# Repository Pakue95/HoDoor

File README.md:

HoDoor is an access control board that uses RFID (13.56MHz) to authenticate users e.g. to enter restricted areas. The firmware repository can be found [here]() (to be released).

## ToDo
* generate Gerber files
* generate new 3d STEP files
* update case-files to v2.1

The work is release as is without any warranties or guarantees. Use on your own risk.

## Hardware

## License

Designed by Patrick Kübler (except for Adafruit PN532 Shield part). Creative Commons Attribution/Share-Alike.

### Adafruit PN532 RFID/NFC Shield for Arduino

The NFC part of the board is based upon the Adafruit PN532 RFID/NFC Shield for Arduino. The design files can be found in the according [repository](https://github.com/adafruit/Adafruit-PN532-RFID-NFC-Shield) and the board can be purchased from [Adafruit](https://www.adafruit.com/product/789).

Following changes were made from the Adafruit design:
* Moved pinheader around (no Arduino Shield compatebility anymore)
* Moved some components and routing
* removed LED power indicator
* no prototyping area
* removed 3.3V regulator (handled by the HoDoor board)

**README from Adafruit PN532 Shield**

>We've taken our popular Adafruit PN532 breakout board and turned it into a shield - the perfect tool for any 13.56MHz RFID or NFC application. The Adafruit NFC shield uses the PN532 chip-set (the most popular NFC chip on the market) and is what is embedded in pretty much every phone or device that does NFC. It can pretty much do it all, such as read and write to tags and cards, communicate with phones (say for payment processing), and 'act' like a NFC tag. If you want to do any sort of embedded NFC work, this is the chip you'll want to use!

>These are the Eagle CAD files for the Adafruit PN532 RFID/NFC Shield for Arduino:

>* http://www.adafruit.com/products/789

>License

>Adafruit invests time and resources providing this open source design, please support Adafruit and open-source hardware by purchasing products from Adafruit!

>All text above must be included in any redistribution

>Designed by Limor Fried/Ladyada and Kevin Townsend for Adafruit Industries. Creative Commons Attribution/Share-Alike, all text above must be included in any redistribution. See license.txt for additional information.

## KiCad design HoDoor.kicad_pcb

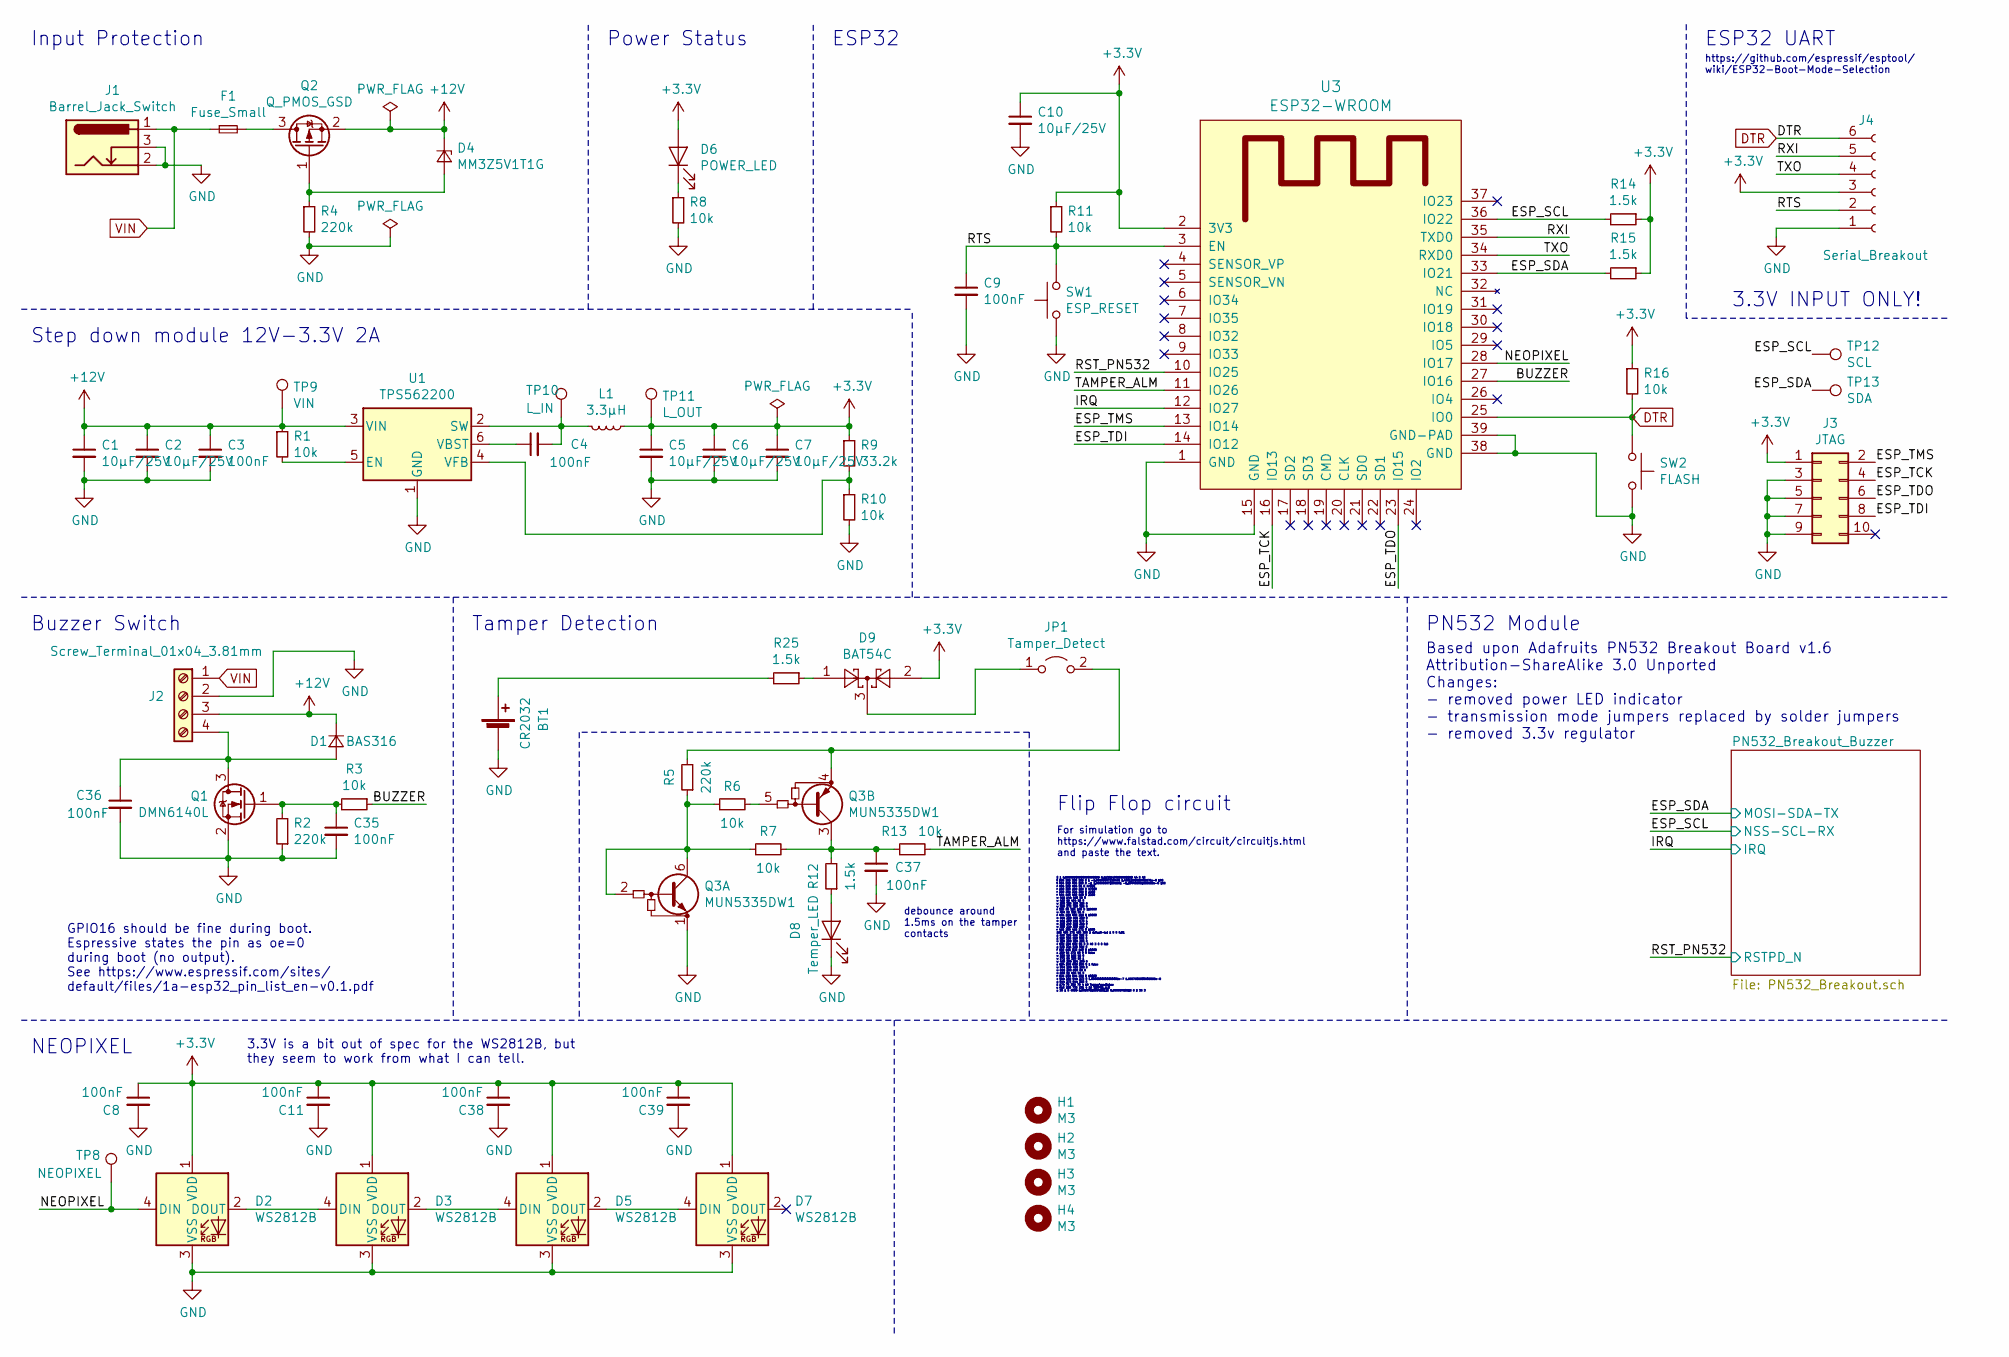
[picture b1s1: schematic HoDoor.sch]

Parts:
BT1: CR2032; BatteryHolder_Keystone_1060_1x2032; Part CR2032-BS-6-1; LCSC C70377
C1, C2, C5, C6, C7, C10: 10µF/25V; C_1206_3216Metric; Part CL31B106KAHVPNE; LCSC C9807
C3, C4, C8, C9, C11, C35, C36, C37, C38, C39: 100nF; C_0603_1608Metric; Part CL10B104KA8NNNC; LCSC C1590
D1: BAS316; D_SOD-323; Part BAS316,115; LCSC C109218
D2, D3, D5, D7: WS2812B; LED_WS2812B_PLCC4_5.0x5.0mm_P3.2mm
D4: MM3Z5V1T1G; D_SOD-323; Part MM3Z5V1T1G; LCSC C75074
D6: POWER_LED; LED_0805_2012Metric_Pad1.15x1.40mm_HandSolder; Part FC-2012HRK-620D; LCSC C84256
D8: Temper_LED; LED_0805_2012Metric_Pad1.15x1.40mm_HandSolder; Part TJ-S2012SW8TGLC0A-A5 TJ-S2012SW8TGLC0A-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; LCSC C192670
D9: BAT54C; SOT-23; LCSC C37704
F1: Fuse_Small; Fuse_1206_3216Metric_Pad1.42x1.75mm_HandSolder
H1, H2, H3, H4: M3; MountingHole_3.2mm_M3_DIN965_Pad
J1: Barrel_Jack_Switch; BarrelJack_Horizontal
J2: Screw_Terminal_01x04_3.81mm; WJ15EDGRC-3.81-4P; Part WJ15EDGRC-3.81-4P + WJ15EDGKB-3.81-4P; LCSC C7245 + C8408
J3: JTAG; Tag-Connect_TC2050-IDC-FP_2x05_P1.27mm_Vertical
J4: Serial_Breakout; PinHeader_1x06_P2.54mm_Horizontal; Part A2541WR-6P; LCSC C225492
JP1: Tamper_Detect; SW_SPST_B3S-1000
L1: 3.3µH; NPIS43LS; Part NPIS43LS3R3MTRF
Q1: DMN6140L; SOT-23; Part DMN6140LQ-7; LCSC C155271
Q2: Q_PMOS_GSD; SOT-23; Part AO3401A; LCSC C15127
Q3: MUN5335DW1; SOT-363_SC-70-6; Part MUN5335DW1T1G; LCSC C99680
R1, R3, R6, R7, R10, R11, R13, R16: 10k; R_0603_1608Metric; Part RC0603FR-0710KL; LCSC C98220
R2, R4, R5: 220k; R_0603_1608Metric; Part RC0603FR-07220KL; LCSC C123420
R8: 10k; R_0603_1608Metric; Part RC0603JR-07330RL; LCSC C105879
R9: 33.2k; R_0603_1608Metric; Part AC0603FR-0733K2L; LCSC C227824
R12, R14, R15, R25: 1.5k; R_0603_1608Metric; Part RC0603FR-071K5L; LCSC C114668
SW1: ESP_RESET; SW_SPST_B3S-1000; Part TSA063G43-250; LCSC C294564
SW2: FLASH; SW_SPST_B3S-1000; Part TSA063G43-250; LCSC C294564
TP8: NEOPIXEL; TestPoint_Pad_D1.0mm
TP9: VIN; TestPoint_Pad_D1.0mm
TP10: L_IN; TestPoint_Pad_D1.0mm
TP11: L_OUT; TestPoint_Pad_D1.0mm
TP12: SCL; TestPoint_Pad_D1.0mm
TP13: SDA; TestPoint_Pad_D1.0mm
U1: TPS562200; SOT-23-6; Part TPS562200DDCR; LCSC C49757
U3: ESP32-WROOM

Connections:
+12V: C1.1, C2.1, C3.1, D1.1 (K), D4.1 (K), J2.3, Q2.2 (S), R1.1, TP9.1, U1.3 (VIN)
/BUZZER: R3.1, U3.27 (IO16)
/ESP_SCL: R14.2, TP12.1, U3.36 (IO22); also elsewhere on the board
/ESP_SDA: R15.2, TP13.1, U3.33 (IO21); also elsewhere on the board
/ESP_TCK: J3.4, U3.16 (IO13)
/ESP_TDI: J3.8, U3.14 (IO12)
/ESP_TDO: J3.6, U3.23 (IO15)
/ESP_TMS: J3.2, U3.13 (IO14)
/IRQ: U3.12 (IO27); also elsewhere on the board
/NEOPIXEL: D2.4 (DIN), TP8.1, U3.28 (IO17)
/RST_PN532: U3.10 (IO25); also elsewhere on the board
/RTS: C9.1, J4.2, R11.2, SW1.2, U3.3 (EN)
/RXI: J4.5, U3.35 (TXD0)
/TAMPER_ALM: R13.2, U3.11 (IO26)
/TXO: J4.4, U3.34 (RXD0)
DTR: J4.6, R16.2, SW2.1, U3.25 (IO0)
GND: BT1.2 (-), C1.2, C2.2, C3.2, C5.2, C6.2, C7.2, C8.2, C9.2, C10.2, C11.2, C35.2, C36.2, C37.2, C38.2, C39.2, D2.3 (VSS), D3.3 (VSS), D5.3 (VSS), D7.3 (VSS), D8.1 (K), J1.2, J1.3, J2.2, J3.3, J3.5, J3.7, J3.9, J4.1, Q1.2 (S), Q3.1 (E1), R2.1, R4.2, R8.2, R10.2, SW1.1, SW2.2, U1.1 (GND), U3.1 (GND), U3.15 (GND), U3.38 (GND), U3.39 (GND-PAD); also elsewhere on the board
unnamed: BT1.1 (+), R25.2
unnamed: C4.1, U1.6 (VBST)
unnamed: C4.2, L1.2, TP10.1, U1.2 (SW)
unnamed: C35.1, Q1.1 (G), R2.2, R3.2
unnamed: C36.1, D1.2 (A), J2.4, Q1.3 (D)
unnamed: C37.1, Q3.3 (C1), R7.2, R12.2, R13.1
unnamed: D2.2 (DOUT), D3.4 (DIN)
unnamed: D3.2 (DOUT), D5.4 (DIN)
unnamed: D4.2 (A), Q2.1 (G), R4.1
unnamed: D5.2 (DOUT), D7.4 (DIN)
unnamed: D6.1 (K), R8.1
unnamed: D8.2 (A), R12.1
unnamed: D9.1, R25.1
unnamed: D9.3, JP1.1 (A)
unnamed: F1.2, Q2.3 (D)
unnamed: JP1.2 (B), Q3.4 (E1), R5.2
unnamed: Q3.2 (B1), Q3.6 (C1), R5.1, R6.1, R7.1
unnamed: Q3.5 (B1), R6.2
unnamed: R1.2, U1.5 (EN)
unnamed: R9.2, R10.1, U1.4 (VFB)
VIN: F1.1, J1.1, J2.1

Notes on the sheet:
Step down module 12V-3.3V 2A
GPIO16 should be fine during boot. Espressive states the pin as oe=0 during boot (no output). See https://www.espressif.com/sites/ default/files/1a-esp32_pin_list_en-v0.1.pdf
3.3V INPUT ONLY!
Input Protection
Power Status
Buzzer Switch
Tamper Detection
PN532 Module
ESP32 UART
NEOPIXEL
https://github.com/espressif/esptool/ wiki/ESP32-Boot-Mode-Selection
$ 1 0.00009999999999999999 0.11331484530668263 44 5 43 t 288 256 320 256 0 1 -2.99999997233476 1.4381236668005676e-8 100 t 464 160 496 160 0 -1 2.999999971598301 -1.154406081838033e-8 100 r 464 160 464 96 0 47000 r 288 320 288 256 0 47000 r 288 256 224 256 0 2200 r 464 160 400 160 0 2200 w 496 144 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
For simulation go to https://www.falstad.com/circuit/circuitjs.html and paste the text.
ESP32
Flip Flop circuit
debounce around 1.5ms on the tamper contacts
3.3V is a bit out of spec for the WS2812B, but they seem to work from what I can tell.
Based upon Adafruits PN532 Breakout Board v1.6 Attribution-ShareAlike 3.0 Unported Changes: - removed power LED indicator - transmission mode jumpers replaced by solder jumpers - removed 3.3v regulator

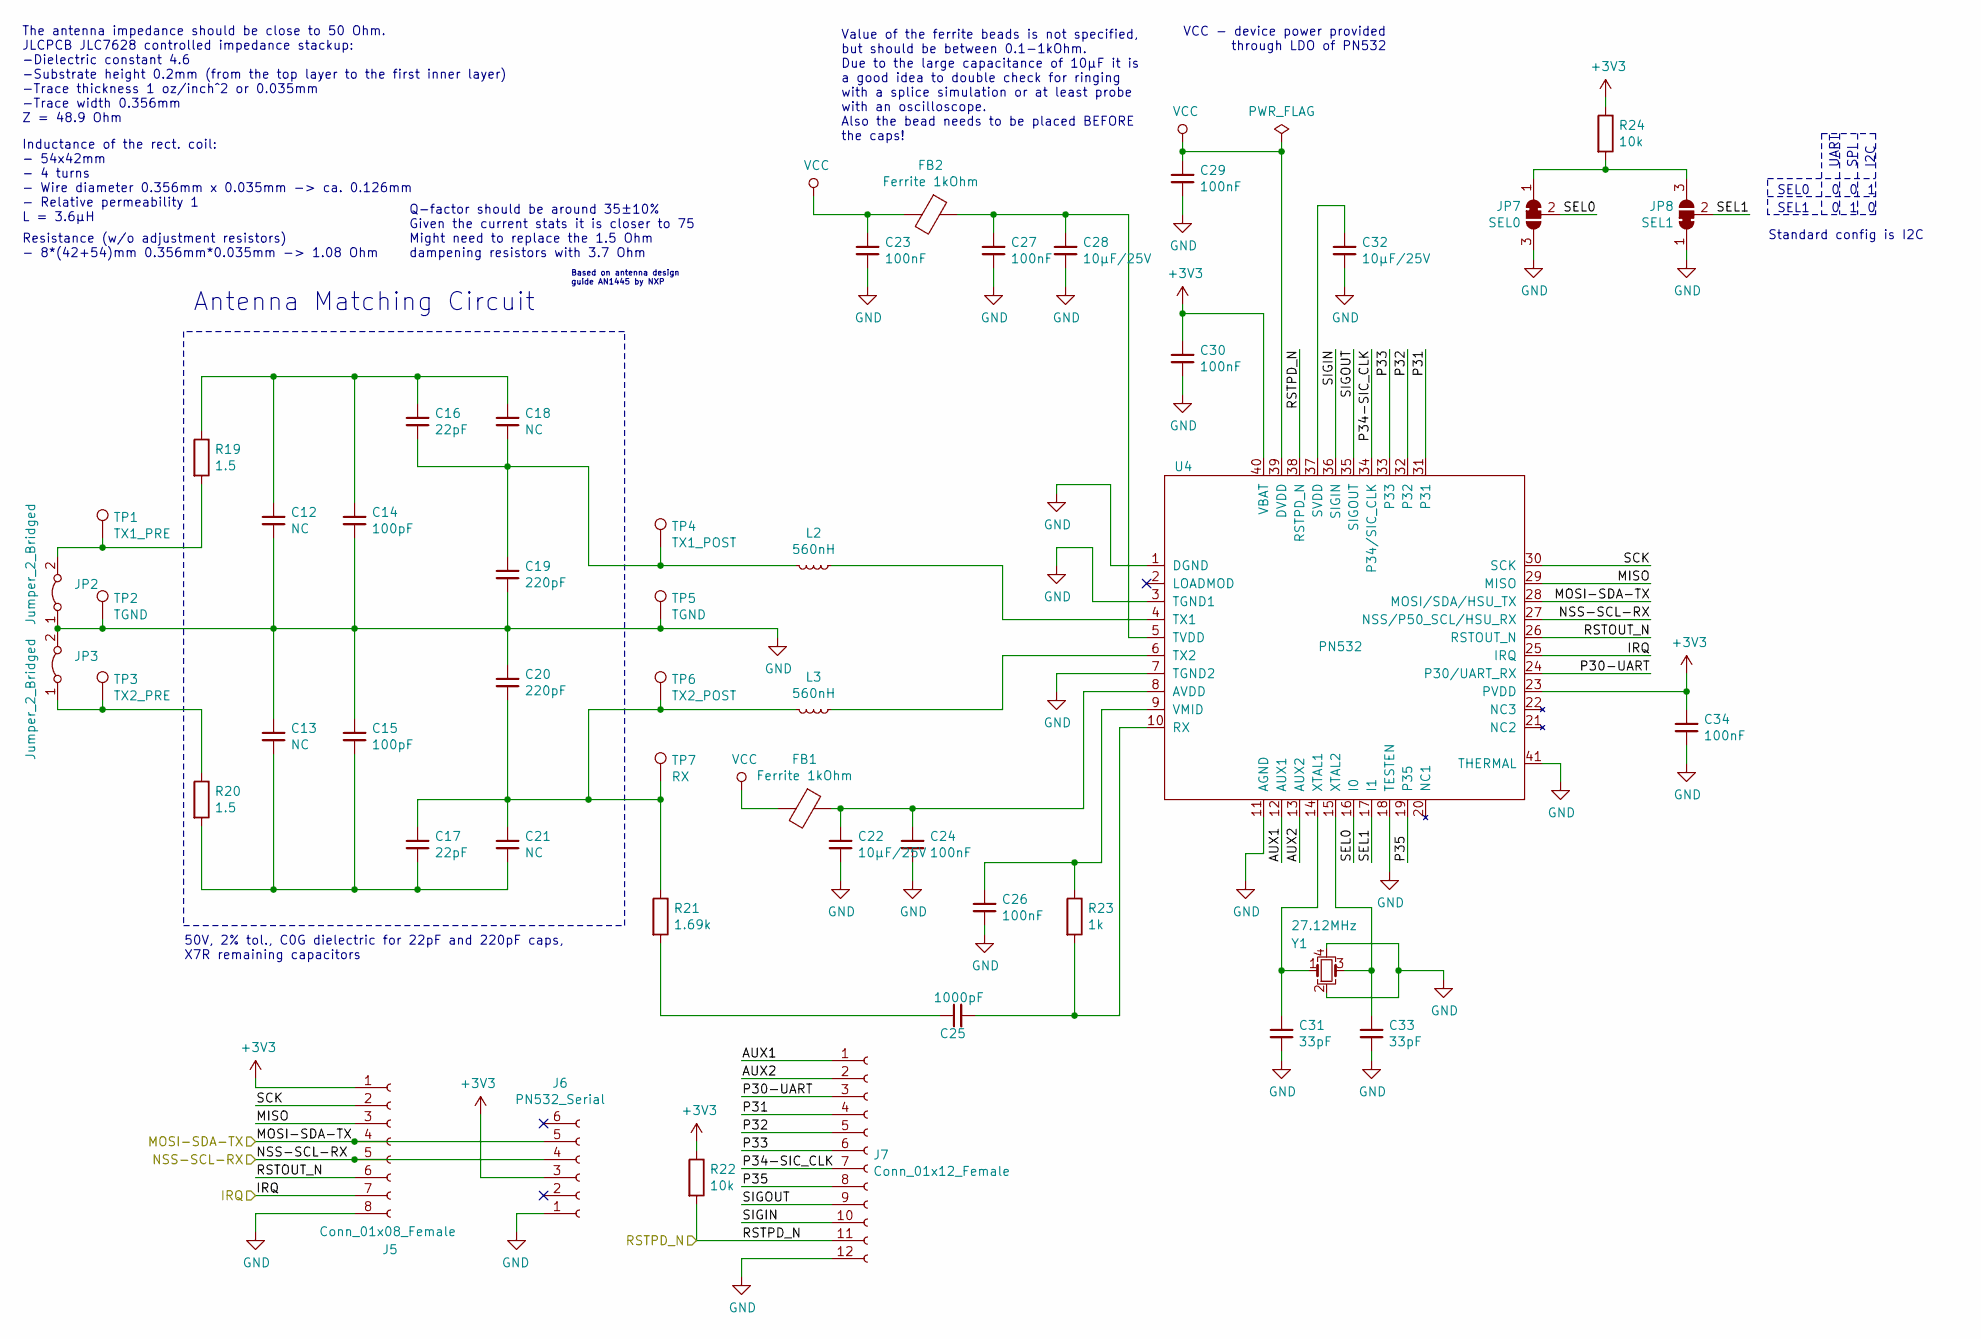
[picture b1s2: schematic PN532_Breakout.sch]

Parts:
C12, C13, C18, C21: NC; C_0603_1608Metric
C14, C15: 100pF; C_0603_1608Metric; Part CC0603GRNPO9BN221; LCSC C327167
C16, C17: 22pF; C_0603_1608Metric; Part CC0603FRNPO9BN220; LCSC C326840
C19, C20: 220pF; C_0603_1608Metric; Part CC0603GRNPO9BN221; LCSC C327167
C22, C28, C32: 10µF/25V; C_1206_3216Metric; Part CL31B106KAHVPNE; LCSC C9807
C23, C24, C26, C27, C29, C30, C34: 100nF; C_0603_1608Metric; Part CL10B104KA8NNNC; LCSC C1590
C25: 1000pF; C_0603_1608Metric; Part CL10C102JB8NNNC; LCSC C163508
C31, C33: 33pF; C_0603_1608Metric; Part CL10C330JB8NNNC; LCSC C1663
FB1, FB2: Ferrite 1kOhm; R_0603_1608Metric; Part CBW160808U102T; LCSC C50069
J5: Conn_01x08_Female; PinHeader_1x08_P2.54mm_Vertical
J6: PN532_Serial; PinHeader_1x06_P2.54mm_Vertical
J7: Conn_01x12_Female; PinHeader_1x12_P2.54mm_Vertical
JP2, JP3: Jumper_2_Bridged; NetTie-2_SMD_Pad0.5mm
JP7: SEL0; SolderJumper-3_P1.3mm_Bridged12_RoundedPad1.0x1.5mm_DRCfix
JP8: SEL1; SolderJumper-3_P1.3mm_Bridged12_RoundedPad1.0x1.5mm_DRCfix
L2, L3: 560nH; R_0603_1608Metric; Part MLJ1608WR56JT000; LCSC C83787
R19, R20: 1.5; R_0603_1608Metric; Part RC0603FR-071R5L; LCSC C245932
R21: 1.69k; R_0603_1608Metric; Part AC0603FR-071K69L; LCSC C227658
R22, R24: 10k; R_0603_1608Metric; Part RC0603FR-0710KL; LCSC C98220
R23: 1k; R_0603_1608Metric; Part RC0603FR-071KL; LCSC C22548
TP1: TX1_PRE; TestPoint_Pad_D1.0mm
TP2, TP5: TGND; TestPoint_Pad_D1.0mm
TP3: TX2_PRE; TestPoint_Pad_D1.0mm
TP4: TX1_POST; TestPoint_Pad_D1.0mm
TP6: TX2_POST; TestPoint_Pad_D1.0mm
TP7: RX; TestPoint_Pad_D1.0mm
U4: PN532; QFN-40-1EP_6x6mm_P0.5mm_EP4.6x4.6mm; Part PN5321A3HN/C106,55; LCSC C28925
Y1: 27.12MHz; 7M-27.120MAAJ-T; Part 7M-27.120MAAJ-T; LCSC C70591

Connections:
/ESP_SCL: J5.5, J6.4, U4.27 (NSS/P50_SCL/HSU_RX); also elsewhere on the board
/ESP_SDA: J5.4, J6.5, U4.28 (MOSI/SDA/HSU_TX); also elsewhere on the board
/IRQ: J5.7, U4.25 (IRQ); also elsewhere on the board
/PN532_Breakout_Buzzer/AUX1: J7.1, U4.12 (AUX1)
/PN532_Breakout_Buzzer/AUX2: J7.2, U4.13 (AUX2)
/PN532_Breakout_Buzzer/MISO: J5.3, U4.29 (MISO)
/PN532_Breakout_Buzzer/P30-UART: J7.3, U4.24 (P30/UART_RX)
/PN532_Breakout_Buzzer/P31: J7.4, U4.31
/PN532_Breakout_Buzzer/P32: J7.5, U4.32
/PN532_Breakout_Buzzer/P33: J7.6, U4.33
/PN532_Breakout_Buzzer/P34-SIC_CLK: J7.7, U4.34 (P34/SIC_CLK)
/PN532_Breakout_Buzzer/P35: J7.8, U4.19 (P35)
/PN532_Breakout_Buzzer/RSTOUT_N: J5.6, U4.26 (RSTOUT_N)
/PN532_Breakout_Buzzer/SCK: J5.2, U4.30 (SCK)
/PN532_Breakout_Buzzer/SEL0: JP7.2 (C), U4.16 (I0)
/PN532_Breakout_Buzzer/SEL1: JP8.2 (C), U4.17 (I1)
/PN532_Breakout_Buzzer/SIGIN: J7.10, U4.36 (SIGIN)
/PN532_Breakout_Buzzer/SIGOUT: J7.9, U4.35 (SIGOUT)
/RST_PN532: J7.11, R22.2, U4.38 (RSTPD_N); also elsewhere on the board
GND: C12.2, C13.1, C14.2, C15.1, C19.2, C20.1, C22.2, C23.2, C24.2, C26.2, C27.2, C28.2, C29.2, C30.2, C31.2, C32.2, C33.2, C34.2, J5.8, J6.1, J7.12, JP2.1 (A), JP3.2 (B), JP7.3 (B), JP8.1 (A), TP2.1, TP5.1, U4.1 (DGND), U4.3 (TGND1), U4.7 (TGND2), U4.11 (AGND), U4.18 (TESTEN), U4.41 (THERMAL), Y1.2, Y1.4; also elsewhere on the board
unnamed: C12.1, C14.1, C16.1, C18.1, R19.1
unnamed: C13.2, C15.2, C17.2, C21.2, R20.2
unnamed: C16.2, C18.2, C19.1, L2.2, TP4.1
unnamed: C17.1, C20.2, C21.1, L3.2, R21.1, TP6.1, TP7.1
unnamed: C22.1, C24.1, FB1.1, U4.8 (AVDD)
unnamed: C25.1, R21.2
unnamed: C25.2, R23.2, U4.10 (RX)
unnamed: C26.1, R23.1, U4.9 (VMID)
unnamed: C27.1, C28.1, FB2.1, U4.5 (TVDD)
unnamed: C31.1, U4.14 (XTAL1), Y1.1
unnamed: C32.1, U4.37 (SVDD)
unnamed: C33.1, U4.15 (XTAL2), Y1.3
unnamed: JP2.2 (B), R19.2, TP1.1
unnamed: JP3.1 (A), R20.1, TP3.1
unnamed: JP7.1 (A), JP8.3 (B), R24.2
unnamed: L2.1, U4.4 (TX1)
unnamed: L3.1, U4.6 (TX2)
VCC: C23.1, C29.1, FB1.2, FB2.2, U4.39 (DVDD)

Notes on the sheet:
VCC - device power provided through LDO of PN532
Value of the ferrite beads is not specified, but should be between 0.1-1kOhm. Due to the large capacitance of 10µF it is a good idea to double check for ringing with a splice simulation or at least probe with an oscilloscope. Also the bead needs to be placed BEFORE the caps!
SEL0
SEL1
UART
SPI
I2C
Antenna Matching Circuit
Standard config is I2C
50V, 2% tol., C0G dielectric for 22pF and 220pF caps, X7R remaining capacitors
The antenna impedance should be close to 50 Ohm. JLCPCB JLC7628 controlled impedance stackup: -Dielectric constant 4.6 -Substrate height 0.2mm (from the top layer to the first inner layer) -Trace thickness 1 oz/inch^2 or 0.035mm -Trace width 0.356mm Z = 48.9 Ohm
Inductance of the rect. coil: - 54x42mm - 4 turns - Wire diameter 0.356mm x 0.035mm -> ca. 0.126mm - Relative permeability 1 L = 3.6µH
Resistance (w/o adjustment resistors) - 8*(42+54)mm 0.356mm*0.035mm -> 1.08 Ohm
Q-factor should be around 35±10% Given the current stats it is closer to 75 Might need to replace the 1.5 Ohm dampening resistors with 3.7 Ohm
Based on antenna design guide AN1445 by NXP

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
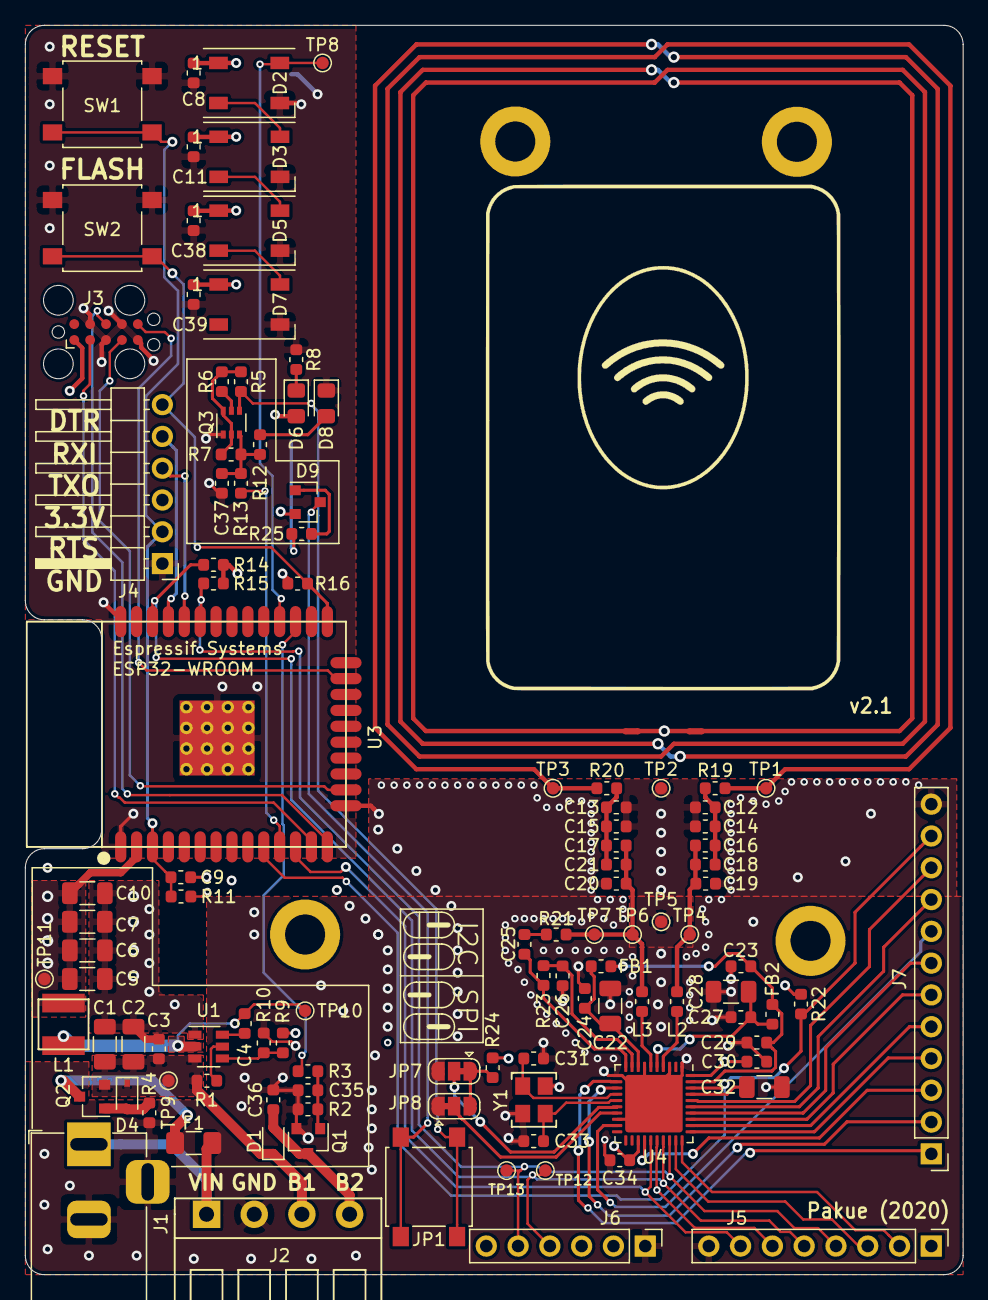
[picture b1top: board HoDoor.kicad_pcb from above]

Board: 4 copper layers, 74.9 x 99.8 mm, 116 parts (1 on the bottom side), 72 nets.

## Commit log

2020-04-20 added README and license
2020-04-20 inital project files port
2020-04-20 removed outdated files
2020-04-20 added some todos
2020-04-23 added Front image
2020-04-23 added front image to README
2020-04-24 added hardware overview image
2020-04-24 Added hardware-info graphic to README
2020-04-27 added schematic pdf and STEP file of the board
